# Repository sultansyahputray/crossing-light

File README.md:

# crossing-light
a miniature version of pedestrian crossing lights utilizing ESP32

Hardware :
1. Green, red, and yellow LED
2. Push button
3. 7-segment
4. ESP32
5. Buzzer
6. Resistor

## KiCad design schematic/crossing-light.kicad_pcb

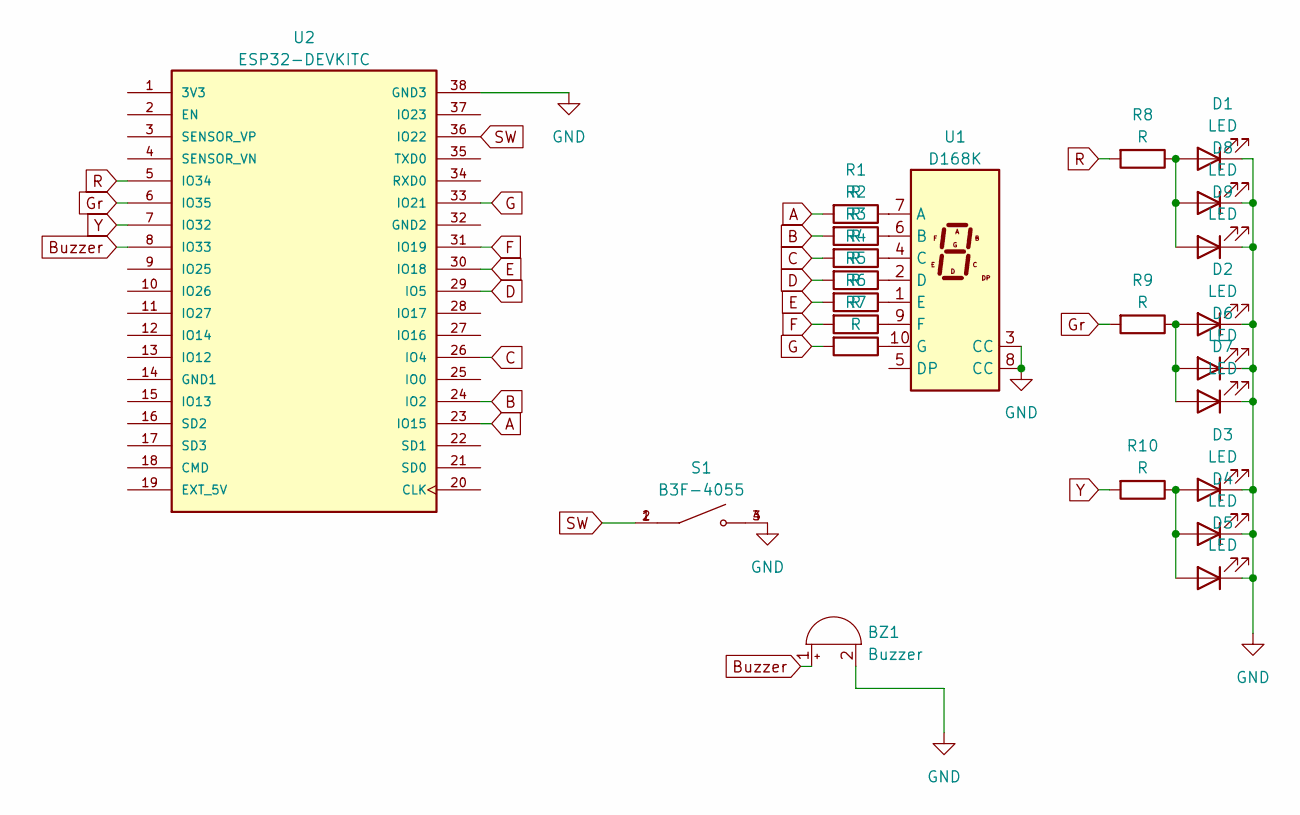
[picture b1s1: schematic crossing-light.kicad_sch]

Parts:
BZ1: Buzzer; Buzzer_15x7.5RM7.6
D1, D2, D3, D4, D5, D6, D7, D8, D9: LED; LED_D5.0mm
R1, R2, R3, R4, R5, R6, R7, R8, R9, R10: R; R_Axial_DIN0411_L9.9mm_D3.6mm_P15.24mm_Horizontal
S1: B3F-4055; SW_B3F-4055; PARTREV A070-E1-08
U1: D168K; D1X8K
U2: ESP32-DEVKITC; MODULE_ESP32-DEVKITC; PARTREV N/A

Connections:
A: R1.2, U2.23 (IO15)
B: R2.2, U2.24 (IO2)
Buzzer: BZ1.1 (-), U2.8 (IO33)
C: R3.2, U2.26 (IO4)
D: R4.2, U2.29 (IO5)
E: R5.2, U2.30 (IO18)
F: R6.2, U2.31 (IO19)
G: R7.2, U2.33 (IO21)
GND: BZ1.2 (+), D1.1 (K), D2.1 (K), D3.1 (K), D4.1 (K), D5.1 (K), D6.1 (K), D7.1 (K), D8.1 (K), D9.1 (K), S1.3, S1.4, U1.3 (CC), U1.8 (CC), U2.38 (GND3)
Gr: R9.2, U2.6 (IO35)
unnamed: D1.2 (A), D8.2 (A), D9.2 (A), R8.1
unnamed: D2.2 (A), D6.2 (A), D7.2 (A), R9.1
unnamed: D3.2 (A), D4.2 (A), D5.2 (A), R10.1
unnamed: R1.1, U1.7 (A)
unnamed: R2.1, U1.6 (B)
unnamed: R3.1, U1.4 (C)
unnamed: R4.1, U1.2 (D)
unnamed: R5.1, U1.1 (E)
unnamed: R6.1, U1.9 (F)
unnamed: R7.1, U1.10 (G)
R: R8.2, U2.5 (IO34)
SW: S1.1, S1.2, U2.36 (IO22)
Y: R10.2, U2.7 (IO32)

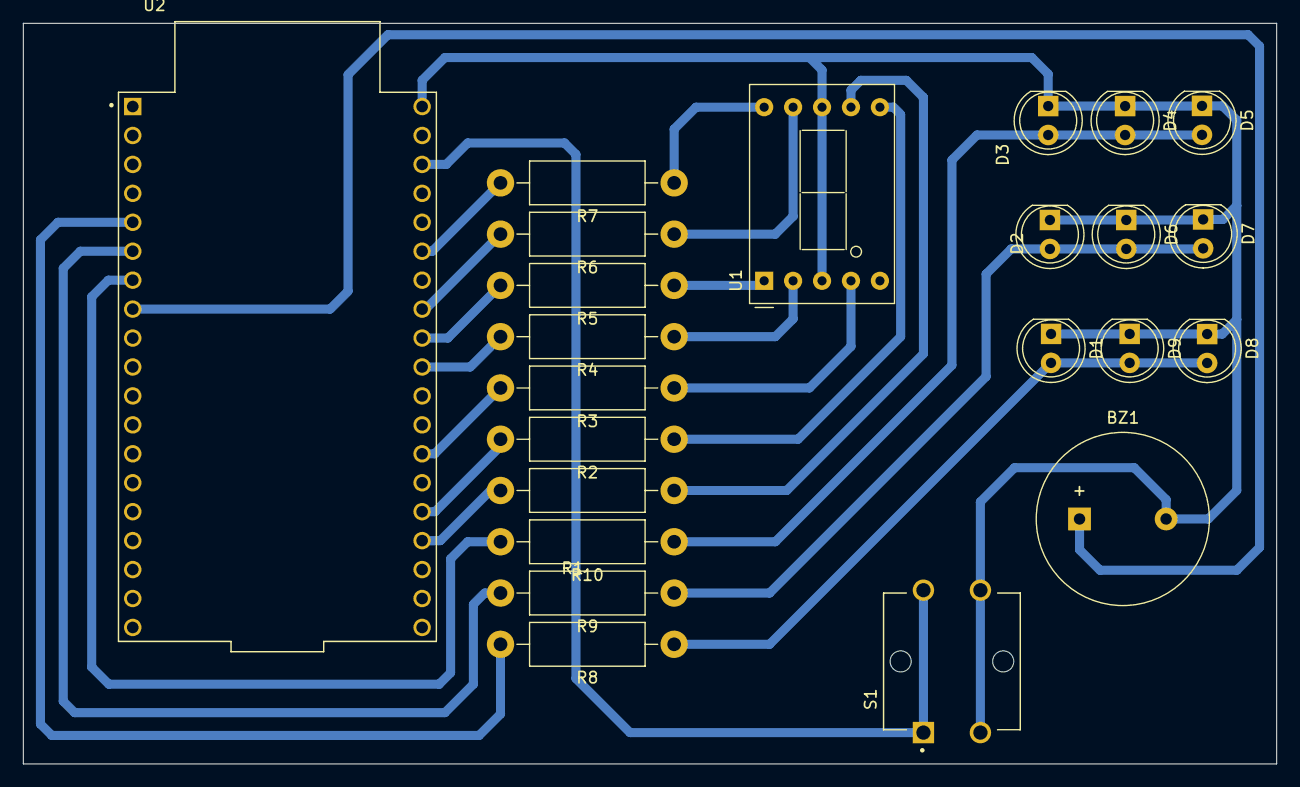
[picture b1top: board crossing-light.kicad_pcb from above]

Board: 2 copper layers, 110.0 x 65.0 mm, 23 parts (0 on the bottom side), 23 nets.

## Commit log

2023-08-27 upload program
2023-08-27 Update list hardware for miniature of pedestrian crossing light
2023-09-03 add schematic
2023-09-03 change camel case to snake case
